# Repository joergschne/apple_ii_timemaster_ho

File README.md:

# apple_ii_timemaster_ho
 Apple II Timemaster II H.O. Clock Card - reloaded

APPLE II forever!

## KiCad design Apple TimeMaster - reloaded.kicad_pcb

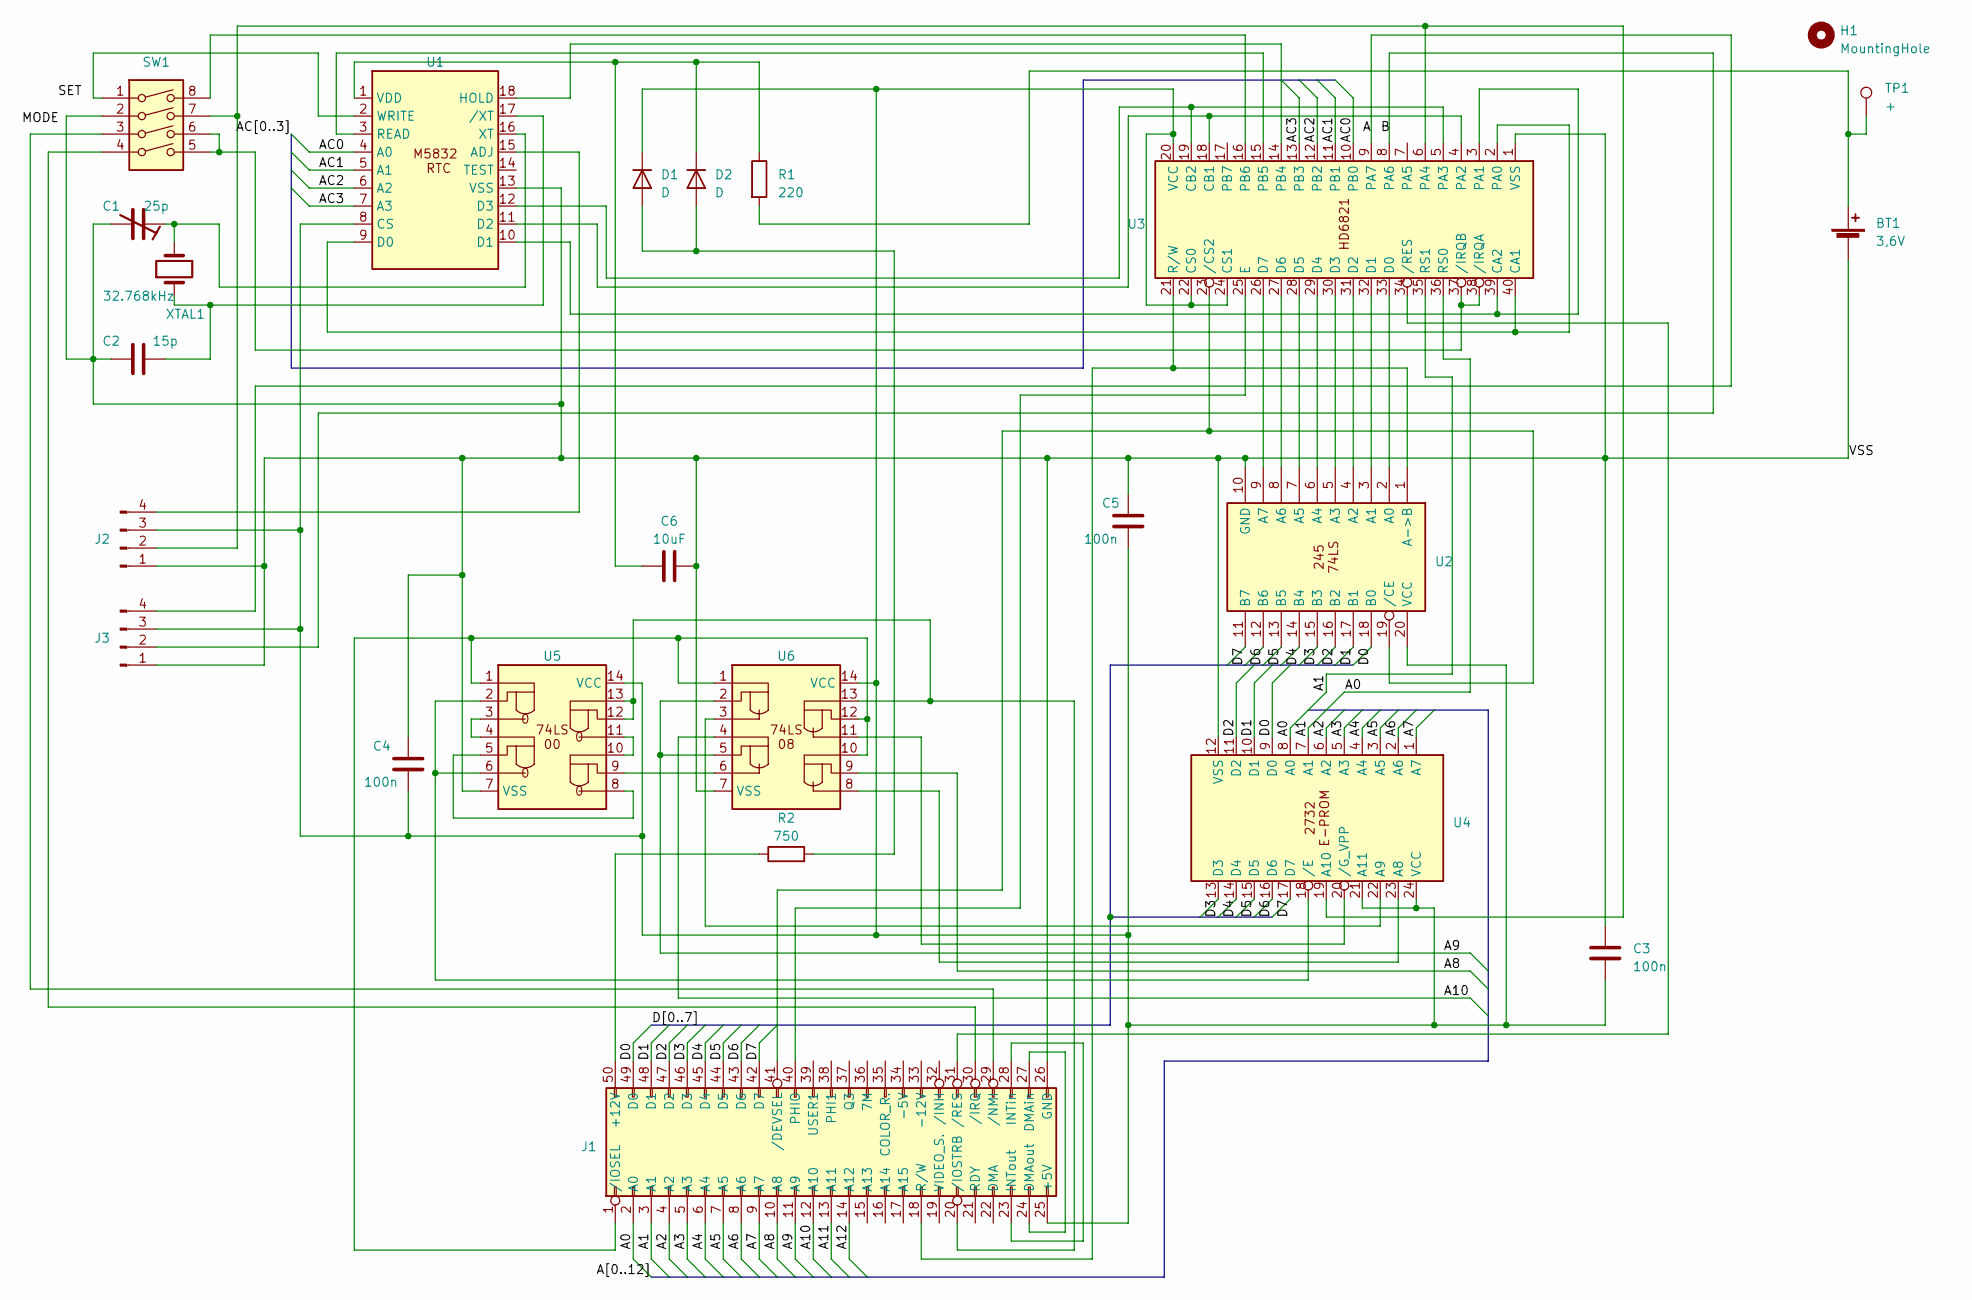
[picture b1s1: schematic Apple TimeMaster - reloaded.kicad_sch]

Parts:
BT1: 3,6V; Varta 55615703012
C1: 25p; Trimmer
C2: 15p; C_Disc_D4.3mm_W1.9mm_P5.00mm
C3, C4, C5: 100n; C_Disc_D4.3mm_W1.9mm_P5.00mm
C6: 10uF; CP_Axial_L10.0mm_D4.5mm_P15.00mm_Horizontal
D1, D2: D; D_DO-34_SOD68_P10.16mm_Horizontal
H1: MountingHole; MountingHole_2.1mm
J1: Apple ][ Bus
J2, J3: Conn_01x04_Pin; Apple_PinHeader_1x04_P2.54mm_Horizontal
R1: 220; R_Axial_DIN0207_L6.3mm_D2.5mm_P10.16mm_Horizontal
R2: 750; R_Axial_DIN0207_L6.3mm_D2.5mm_P10.16mm_Horizontal
SW1: SW_DIP_x04; DIP-8_W7.62mm
TP1: +; TestPoint_Pad_D2.0mm
U1: DIP-18_W7.62mm_LongPads
U2: DIP-20_W7.62mm_LongPads
U3: DIP-40_W15.24mm_LongPads
U4: DIP-24_W15.24mm_LongPads
U5, U6: DIP-14_W7.62mm_LongPads
XTAL1: 32.768kHz; Crystal

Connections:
/A0: J1.2 (A0), U3.36 (RS0), U4.8 (A0)
/A1: J1.3 (A1), U3.35 (RS1), U4.7 (A1)
/A2: J1.4 (A2), U4.6 (A2)
/A3: J1.5 (A3), U4.5 (A3)
/A4: J1.6 (A4), U4.4 (A4)
/A5: J1.7 (A5), U4.3 (A5)
/A6: J1.8 (A6), U4.2 (A6)
/A7: J1.9 (A7), U4.1 (A7)
/A8: J1.10 (A8), U6.9
/A9: J1.11 (A9), U6.2, U6.5
/A10: J1.12 (A10), U6.4
/A11: J1.13 (A11)
/A12: J1.14 (A12)
/AC0: U1.4 (A0), U3.10 (PB0)
/AC1: U1.5 (A1), U3.11 (PB1)
/AC2: U1.6 (A2), U3.12 (PB2)
/AC3: U1.7 (A3), U3.13 (PB3)
/D0: J1.49 (D0), U2.18 (B0), U4.9 (D0)
/D1: J1.48 (D1), U2.17 (B1), U4.10 (D1)
/D2: J1.47 (D2), U2.16 (B2), U4.11 (D2)
/D3: J1.46 (D3), U2.15 (B3), U4.13 (D3)
/D4: J1.45 (D4), U2.14 (B4), U4.14 (D4)
/D5: J1.44 (D5), U2.13 (B5), U4.15 (D5)
/D6: J1.43 (D6), U2.12 (B6), U4.16 (D6)
/D7: J1.42 (D7), U2.11 (B7), U4.17 (D7)
/VSS: BT1.2 (-), C1.2, C2.1, C3.1, C4.1, C5.1, C6.2, J1.26 (GND), J2.1, J3.1, SW1.2, U1.13 (VSS), U2.10 (GND), U3.1 (VSS), U4.12 (VSS), U5.7 (VSS), U6.7 (VSS)
unnamed: BT1.1 (+), R1.2, TP1.1
unnamed: D1.2 (A), D2.2 (A), R2.2
unnamed: C3.2, C4.2, C5.2, D1.1 (K), J1.25 (+5V), J2.3, J3.3, U1.8 (CS), U2.20 (VCC), U3.20 (VCC), U3.22 (CS0), U3.24 (CS1), U4.21 (A11), U4.24 (VCC), U5.14 (VCC), U6.14 (VCC)
unnamed: C6.1, D2.1 (K), R1.1, U1.1 (VDD)
unnamed: J1.50 (+12V), R2.1
unnamed: J1.24 (DMAout), J1.27 (DMAin)
unnamed: J1.23 (INTout), J1.28 (INTin)
unnamed: J1.40 (PHIO), U3.25 (E)
unnamed: J1.18 (R/W), U2.1 (A->B), U3.21 (R/W)
unnamed: J1.41 (/DEVSEL), U2.19 (/CE), U3.23 (/CS2)
unnamed: J1.1 (/IOSEL), U5.1, U6.1, U6.10, U6.12
unnamed: J1.20 (/IOSTRB), U5.12, U5.13, U6.13
unnamed: J1.30 (/IRQ), SW1.4
unnamed: J1.29 (/NMI), SW1.3
unnamed: J1.31 (/RES), U3.34 (/RES)
unnamed: J2.2, SW1.7, U3.6 (PA4), U4.19 (A10)
unnamed: J2.4, U1.15 (ADJ)
unnamed: J3.2, U3.8 (PA6)
unnamed: J3.4, U3.9 (PA7)
unnamed: U1.9 (D0), U3.2 (PA0), U3.40 (CA1)
unnamed: U1.10 (D1), U3.3 (PA1), U3.39 (CA2)
unnamed: U1.11 (D2), U3.4 (PA2), U3.18 (CB1)
unnamed: U1.12 (D3), U3.5 (PA3), U3.19 (CB2)
unnamed: U1.18 (HOLD), U3.14 (PB4)
unnamed: U1.3 (READ), U3.15 (PB5)
unnamed: SW1.1, U1.2 (WRITE)
unnamed: C1.1, U1.16 (XT), XTAL1.2
unnamed: C2.2, U1.17 (/XT), XTAL1.1
unnamed: U2.2 (A0), U3.33 (D0)
unnamed: U2.3 (A1), U3.32 (D1)
unnamed: U2.4 (A2), U3.31 (D2)
unnamed: U2.5 (A3), U3.30 (D3)
unnamed: U2.6 (A4), U3.29 (D4)
unnamed: U2.7 (A5), U3.28 (D5)
unnamed: U2.8 (A6), U3.27 (D6)
unnamed: U2.9 (A7), U3.26 (D7)
unnamed: SW1.8, U3.16 (PB6)
unnamed: SW1.5, SW1.6, U3.37 (/IRQB), U3.38 (/IRQA)
unnamed: U4.23 (A8), U6.8
unnamed: U4.22 (A9), U6.3
unnamed: U4.18 (/E), U5.2, U5.6
unnamed: U4.20 (/G_VPP), U6.11
unnamed: U5.3, U5.4
unnamed: U5.5, U5.8
unnamed: U5.9, U6.6
unnamed: U5.10, U5.11

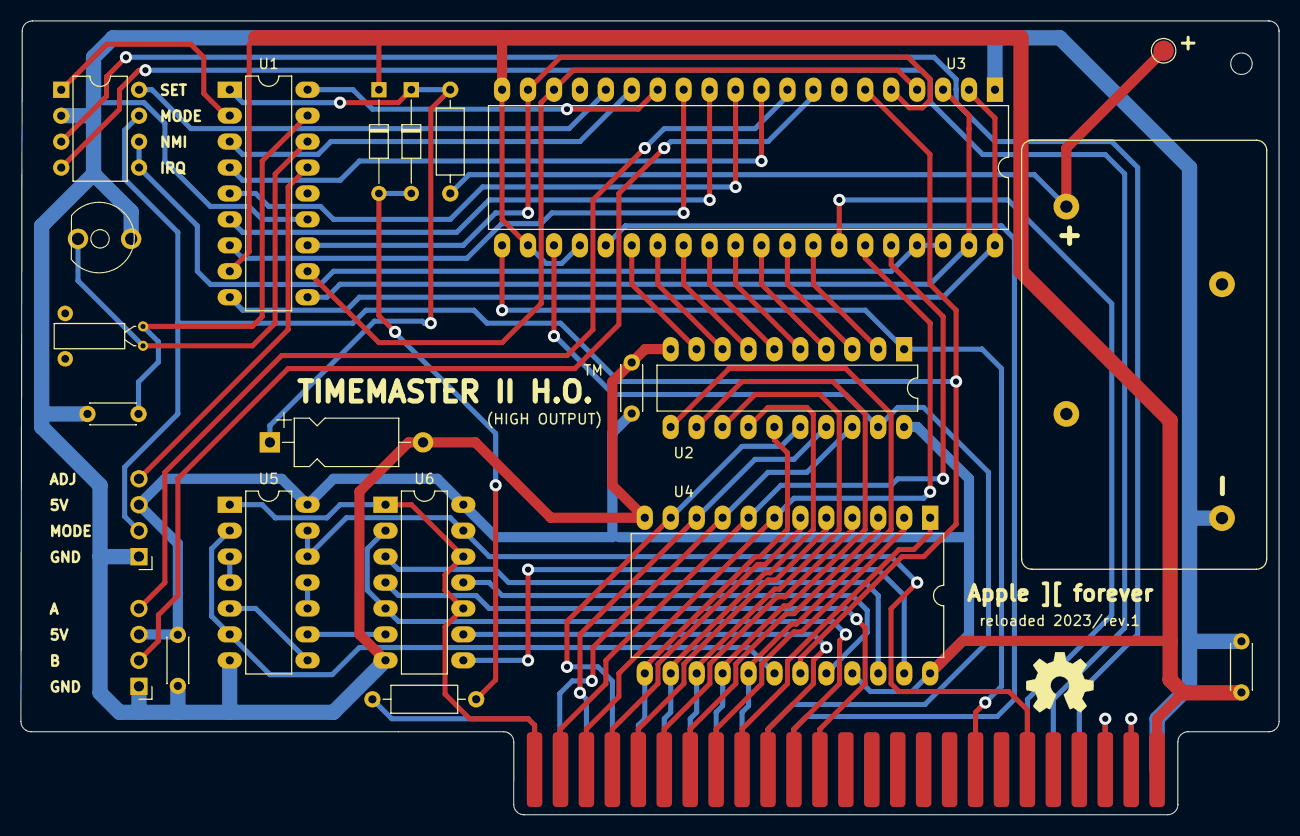
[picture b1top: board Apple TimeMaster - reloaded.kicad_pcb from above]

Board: 2 copper layers, 123.2 x 77.7 mm, 24 parts (0 on the bottom side), 70 nets.

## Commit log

2024-04-27 initian commit
